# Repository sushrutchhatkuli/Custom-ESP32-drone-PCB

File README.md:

# Cheap Drone

I designed a custom drone flight controller PCB based on the ESP32-WROOM-32. The board uses USB-C charging, regulated 3.3 V power delivery, and onboard IMU sensing using the MPU-6050. The PCB is currently being fabricated, and I am actively working on automatic stabilization code for my motors.

## Overview
The goal of this project was to design a low-cost, custom flight controller PCB for a quadcopter drone while gaining hands-on experience with power management, embedded hardware design, and PCB layout. Instead of using a real controller, I wanted to use a free app that can be downloaded from the App store since ESP32 supports Wifi and Bluetooth.

The design is organized into three main parts:
- Power management
- ESP32 control and programming
- Motors and sensors

## Power Management
Power management was a major focus of this design. The board uses a battery charging circuit along with a voltage regulator to safely power all components. The incoming voltage is regulated to 3.3 V using the MIC5219-3.3YM5, which supplies power to both the ESP32 and the MPU-6050.

When the board is connected to USB-C, the voltage passes through a Schottky diode (SS34) and reaches the gate of an AO3401A P-channel MOSFET. This turns the MOSFET off and disconnects the battery (+VBatt) from the system, allowing the drone to run directly from USB power while the battery is charging.

Battery charging is handled by the TP4056, which safely manages the LiPo charging process. Two LEDs connected to the TP4056 indicate whether the battery is charging or fully charged. When the USB cable is unplugged, the MOSFET automatically turns on, reconnecting the battery so it can power the system. Decoupling capacitors are placed throughout the power rails to reduce noise and improve voltage stability.

## ESP32 Control and Programming
The +VBUS line is routed before the voltage regulator so it can supply 5 V power to the CP2102 USB-to-UART converter, which requires a higher voltage than the ESP32.

The USB data lines (D+ and D−) carry compiled code from the computer to the CP2102. The CP2102 converts this USB data into UART signals (TX and RX) that are sent to the ESP32. The RTS and DTR signals from the CP2102 pass through a 2N7002DW MOSFET, which automatically controls the EN and BOOT pins of the ESP32 during programming. This allows the ESP32 to enter firmware upload mode automatically and return to normal operation later without manual button presses.

The ESP32 acts as the main controller of the drone. It processes sensor data, controls motor outputs, and manages the overall behavior of the system. Orientation data from the MPU-6050 is used to adjust motor speeds for stabilization. I also added a UART2 (RXD2/TXD2) connector for future expansion and a four-channel SRV connector for motor control signals. Decoupling capacitors here on the 3.3 V rail help minimize noise from switching components.

## Motors and Sensors
The MPU-6050 is used as a 6-axis IMU to measure acceleration and angular velocity. It communicates with the ESP32 over I²C using the SDA and SCL lines, with pull-up resistors included to ensure reliable communication. The sensor operates at 3.3 V and is powered from the regulated supply.

The MPU-6050 does not control the motors directly. Instead, it sends motion data to the ESP32, which determines how each motor should respond to keep the drone stable. The motors are powered directly from the battery (+VBatt) because they require higher current than the logic circuitry.

Each motor is driven using an SI2302 N-channel MOSFET, allowing low-power control signals from the ESP32 to switch high-current motor loads. The MOSFET gates are driven by the ESP32, the sources are connected to ground, and the drains connect to the motors and battery supply. Since motors generate voltage spikes when switching, flyback diodes are included to protect the MOSFETs and surrounding components.

## Current Status
- Schematic and PCB design completed
- All ERC and DRC checks passed
- PCB fabrication and soldering the components in progress
- Automatic stabilization firmware under development

## Future Work
- Adding object-tracking cameras
- 3D Mapping using SLAM
- Perform flight testing and tuning
- Rev B PCB improvements based on test results

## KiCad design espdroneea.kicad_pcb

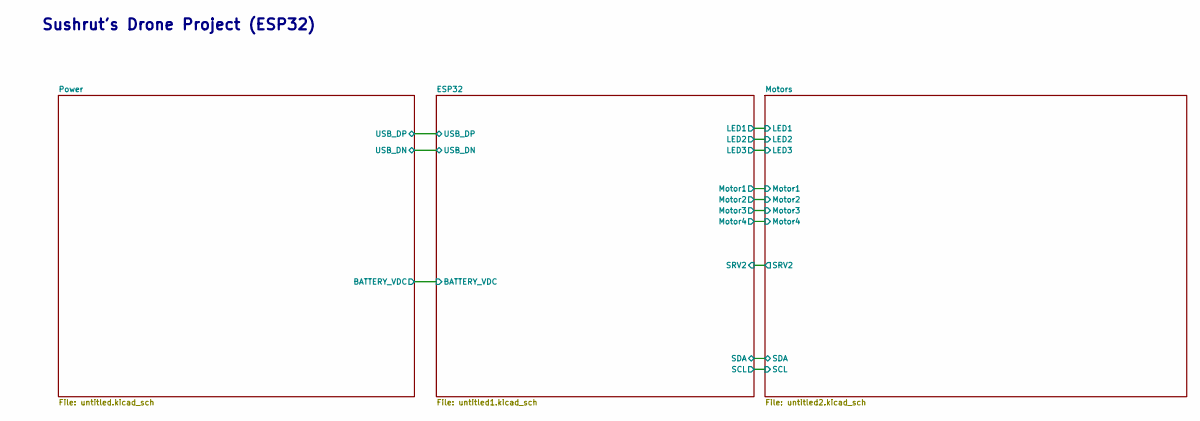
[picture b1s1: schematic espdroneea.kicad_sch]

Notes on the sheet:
Sushrut's Drone Project (ESP32)

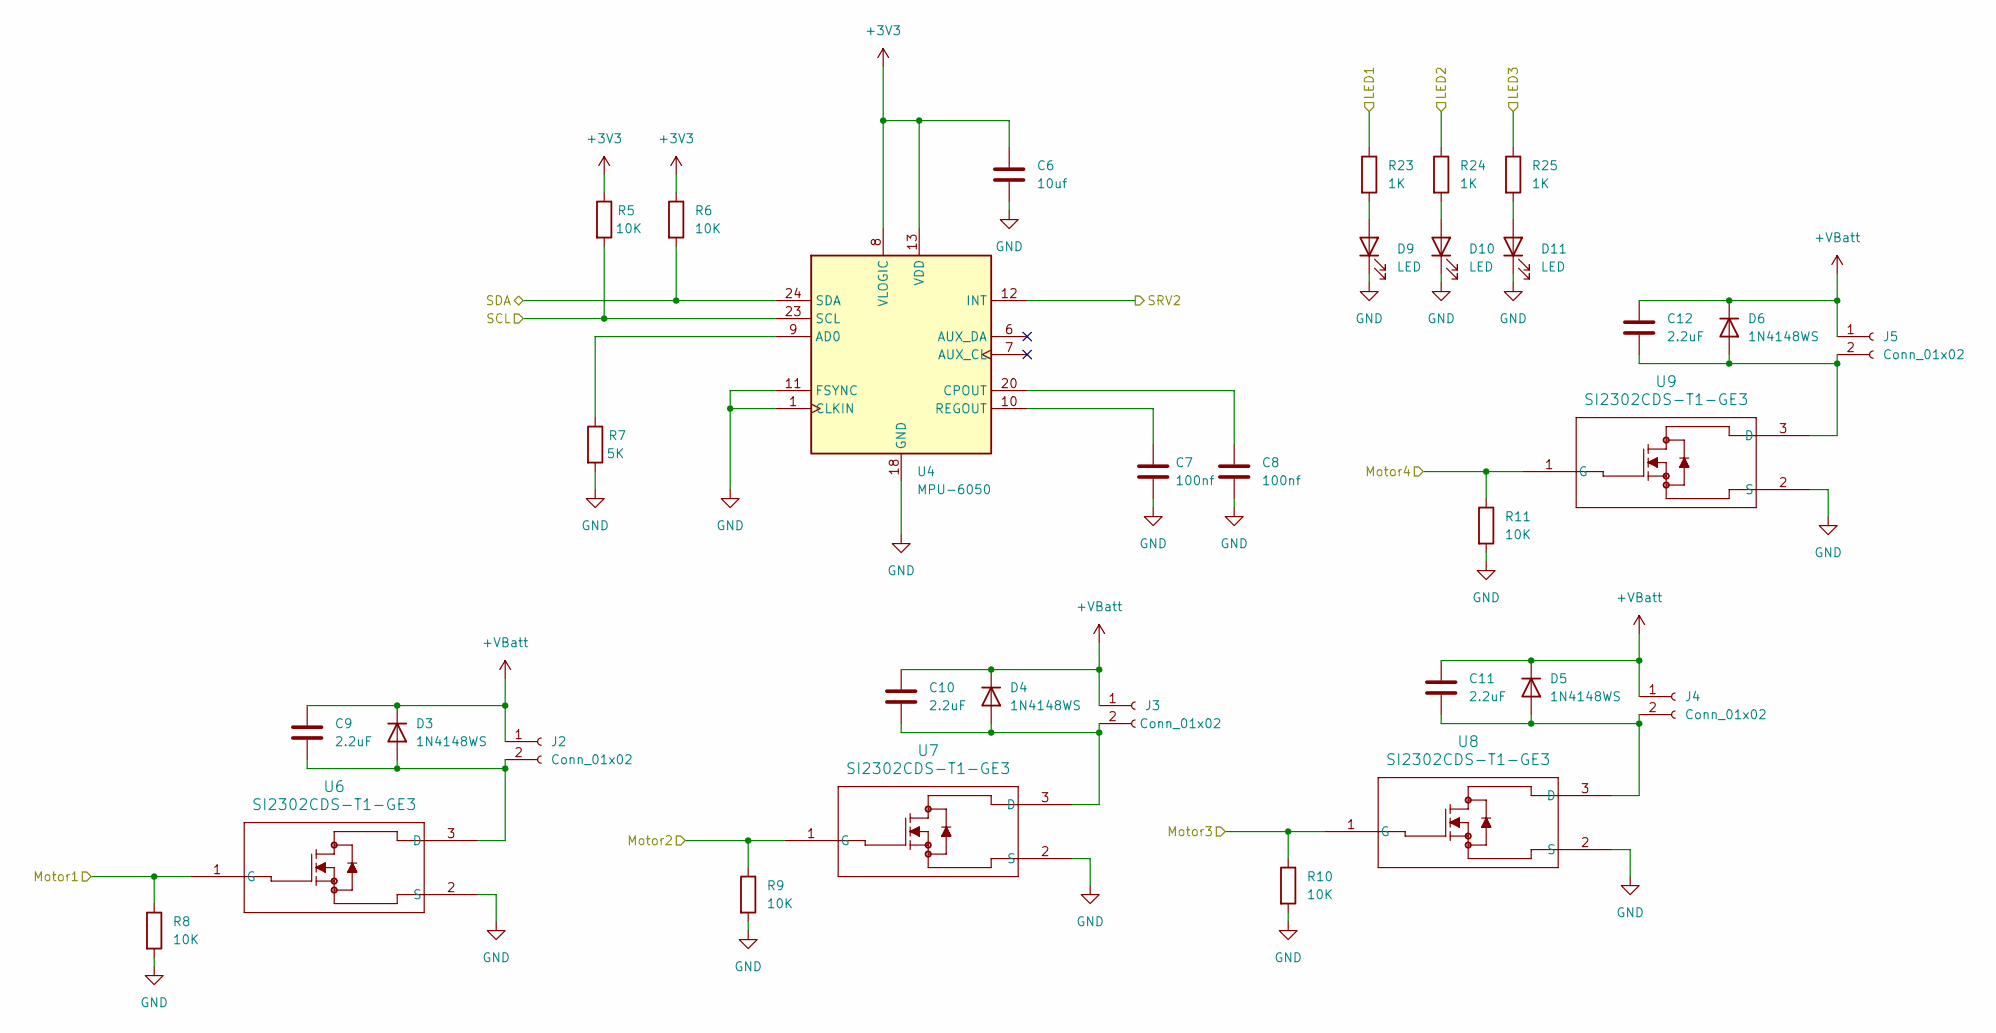
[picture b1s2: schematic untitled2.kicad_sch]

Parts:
C6: 10uf; C_0603_1608Metric
C7, C8: 100nf; C_0603_1608Metric
C9, C10, C11, C12: 2.2uF; C_0603_1608Metric
D3, D4, D5, D6: 1N4148WS; D_SOD-323
D9, D10, D11: LED; LED_0603_1608Metric
J2, J3, J4, J5: Conn_01x02; JST_GH_SM02B-GHS-TB_1x02-1MP_P1.25mm_Horizontal
R5, R6, R8, R9, R10, R11: 10K; R_0603_1608Metric
R7: 5K; R_0603_1608Metric
R23, R24, R25: 1K; R_0603_1608Metric
U4: MPU-6050; InvenSense_QFN-24_4x4mm_P0.5mm
U6, U7, U8, U9: SI2302CDS-T1-GE3; TO-236_VIS

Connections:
+3V3: C6.1, R5.1, R6.1, U4.8 (VLOGIC), U4.13 (VDD); also elsewhere on the board
+VBatt: C9.1, C10.1, C11.1, C12.1, D3.1 (K), D4.1 (K), D5.1 (K), D6.1 (K), J2.1, J3.1, J4.1, J5.1; also elsewhere on the board
/ESP32/LED1: R23.1; also elsewhere on the board
/ESP32/LED2: R24.1; also elsewhere on the board
/ESP32/LED3: R25.1; also elsewhere on the board
/ESP32/Motor1: R8.1, U6.1 (G); also elsewhere on the board
/ESP32/Motor2: R9.1, U7.1 (G); also elsewhere on the board
/ESP32/Motor3: R10.1, U8.1 (G); also elsewhere on the board
/ESP32/Motor4: R11.1, U9.1 (G); also elsewhere on the board
/ESP32/SCL: R5.2, U4.23 (SCL); also elsewhere on the board
/ESP32/SDA: R6.2, U4.24 (SDA); also elsewhere on the board
/ESP32/SRV2: U4.12 (INT); also elsewhere on the board
GND: C6.2, C7.2, C8.2, D9.1 (K), D10.1 (K), D11.1 (K), R7.2, R8.2, R9.2, R10.2, R11.2, U4.1 (CLKIN), U4.11 (FSYNC), U4.18 (GND), U6.2 (S), U7.2 (S), U8.2 (S), U9.2 (S); also elsewhere on the board
unnamed: C9.2, D3.2 (A), J2.2, U6.3 (D)
unnamed: C10.2, D4.2 (A), J3.2, U7.3 (D)
unnamed: C11.2, D5.2 (A), J4.2, U8.3 (D)
unnamed: C12.2, D6.2 (A), J5.2, U9.3 (D)
unnamed: D9.2 (A), R23.2
unnamed: D10.2 (A), R24.2
unnamed: D11.2 (A), R25.2
unnamed: R7.1, U4.9 (AD0)
unnamed: C8.1, U4.20 (CPOUT)
unnamed: C7.1, U4.10 (REGOUT)

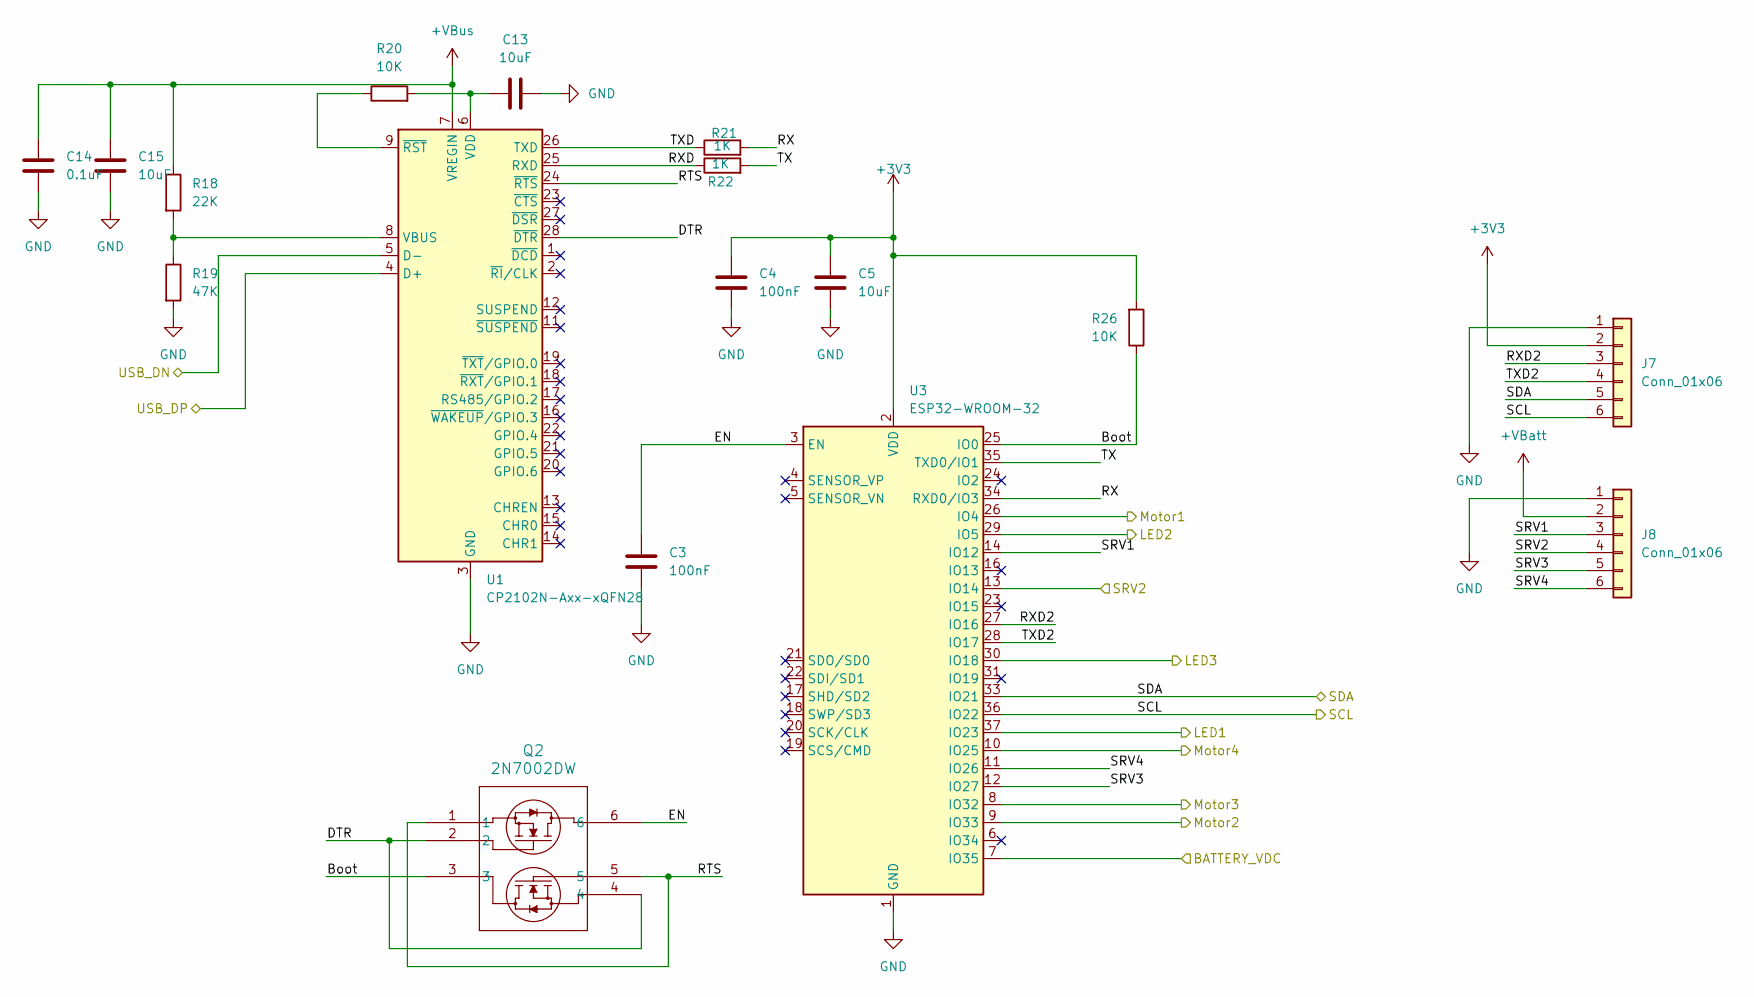
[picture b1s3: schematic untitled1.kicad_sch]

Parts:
C3, C4: 100nF; C_0603_1608Metric
C5, C13, C15: 10uF; C_0603_1608Metric
C14: 0.1uF; C_0603_1608Metric
J7, J8: Conn_01x06; PinHeader_1x06_P2.54mm_Vertical
Q2: 2N7002DW; SOT-23-6
R18: 22K; R_0603_1608Metric
R19: 47K; R_0603_1608Metric
R20, R26: 10K; R_0603_1608Metric
R21, R22: 1K; R_0603_1608Metric
U1: CP2102N-Axx-xQFN28; QFN-28-1EP_5x5mm_P0.5mm_EP3.35x3.35mm
U3: ESP32-WROOM-32

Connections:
+3V3: C4.1, C5.1, J7.2, R26.2, U3.2 (VDD); also elsewhere on the board
+VBatt: J8.2; also elsewhere on the board
+VBus: C14.1, C15.1, R18.1, U1.7 (VREGIN); also elsewhere on the board
/ESP32/BATTERY_VDC: U3.7 (IO35); also elsewhere on the board
/ESP32/Boot: Q2.3, R26.1, U3.25 (IO0)
/ESP32/DTR: Q2.2, Q2.4, U1.28 (~DTR)
/ESP32/EN: C3.1, Q2.6, U3.3 (EN)
/ESP32/LED1: U3.37 (IO23); also elsewhere on the board
/ESP32/LED2: U3.29 (IO5); also elsewhere on the board
/ESP32/LED3: U3.30 (IO18); also elsewhere on the board
/ESP32/Motor1: U3.26 (IO4); also elsewhere on the board
/ESP32/Motor2: U3.9 (IO33); also elsewhere on the board
/ESP32/Motor3: U3.8 (IO32); also elsewhere on the board
/ESP32/Motor4: U3.10 (IO25); also elsewhere on the board
/ESP32/RTS: Q2.1, Q2.5, U1.24 (~RTS)
/ESP32/RX: R21.2, U3.34 (RXD0/IO3)
/ESP32/RXD: R22.1, U1.25 (RXD)
/ESP32/RXD2: J7.3, U3.27 (IO16)
/ESP32/SCL: J7.6, U3.36 (IO22); also elsewhere on the board
/ESP32/SDA: J7.5, U3.33 (IO21); also elsewhere on the board
/ESP32/SRV1: J8.3, U3.14 (IO12)
/ESP32/SRV2: J8.4, U3.13 (IO14); also elsewhere on the board
/ESP32/SRV3: J8.5, U3.12 (IO27)
/ESP32/SRV4: J8.6, U3.11 (IO26)
/ESP32/TX: R22.2, U3.35 (TXD0/IO1)
/ESP32/TXD: R21.1, U1.26 (TXD)
/ESP32/TXD2: J7.4, U3.28 (IO17)
/ESP32/USB_DN: U1.5 (D-); also elsewhere on the board
/ESP32/USB_DP: U1.4 (D+); also elsewhere on the board
GND: C3.2, C4.2, C5.2, C13.2, C14.2, C15.2, J7.1, J8.1, R19.2, U1.3 (GND), U1.29 (GND), U3.1 (GND), U3.15 (GND), U3.38 (GND), U3.39 (GND); also elsewhere on the board
unnamed: R18.2, R19.1, U1.8 (VBUS)
unnamed: C13.1, R20.2, U1.6 (VDD)
unnamed: R20.1, U1.9 (~RST)

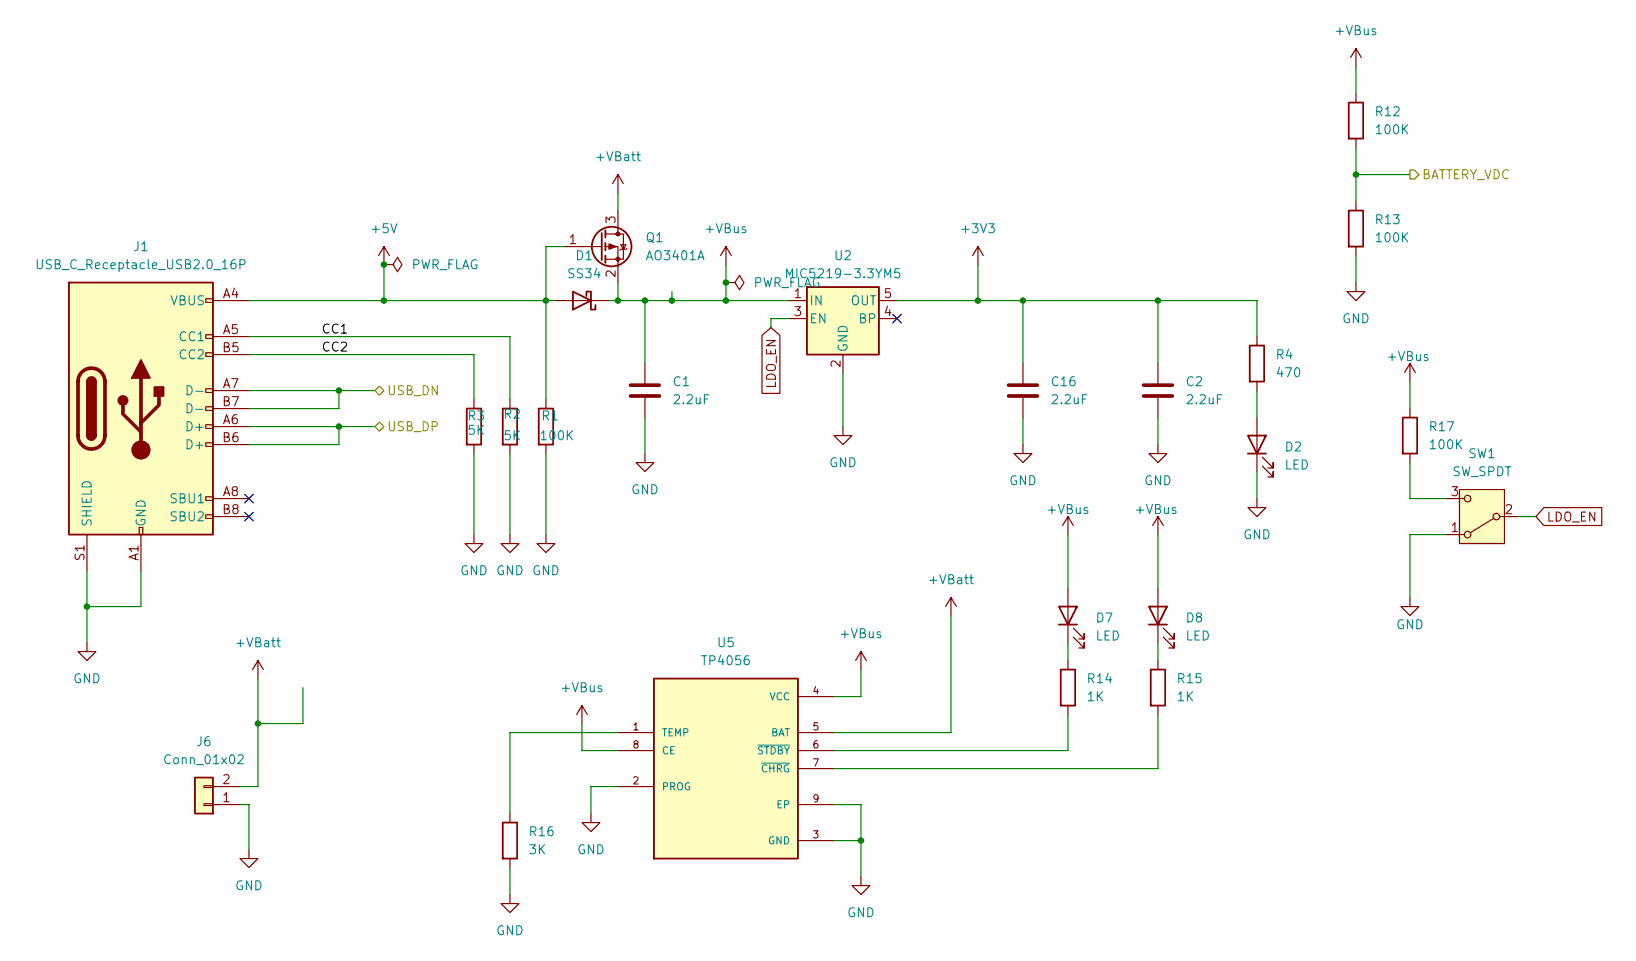
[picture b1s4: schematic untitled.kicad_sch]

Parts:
C1, C2, C16: 2.2uF; C_0603_1608Metric
D1: SS34; D_SMA
D2, D7, D8: LED; LED_0603_1608Metric
J1: USB_C_Receptacle_USB2.0_16P; USB_C_Receptacle_HRO_TYPE-C-31-M-12
J6: Conn_01x02; JST_GH_SM02B-GHS-TB_1x02-1MP_P1.25mm_Horizontal
Q1: AO3401A; SOT-23
R1, R12, R13, R17: 100K; R_0603_1608Metric
R2, R3: 5K; R_0603_1608Metric
R4: 470; R_0603_1608Metric
R14, R15: 1K; R_0603_1608Metric
R16: 3K; R_0603_1608Metric
SW1: SW_SPDT; SW_SPDT_PCM12
U2: MIC5219-3.3YM5; SOT-23-5
U5: TP4056; SOP127P600X175-9N

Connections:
+3V3: C2.1, C16.1, R4.1, U2.5 (OUT); also elsewhere on the board
+5V: D1.2 (A), J1.A4 (VBUS), J1.A9 (VBUS), J1.B4 (VBUS), J1.B9 (VBUS), Q1.1 (G), R1.1
+VBatt: J6.2, Q1.3 (D), U5.5 (BAT); also elsewhere on the board
+VBus: C1.1, D1.1 (K), D7.2 (A), D8.2 (A), Q1.2 (S), R12.1, R17.1, U2.1 (IN), U5.4 (VCC), U5.8 (CE); also elsewhere on the board
/ESP32/BATTERY_VDC: R12.2, R13.1; also elsewhere on the board
/ESP32/USB_DN: J1.A7 (D-), J1.B7 (D-); also elsewhere on the board
/ESP32/USB_DP: J1.A6 (D+), J1.B6 (D+); also elsewhere on the board
/Power/CC1: J1.A5 (CC1), R2.1
/Power/CC2: J1.B5 (CC2), R3.1
GND: C1.2, C2.2, C16.2, D2.1 (K), J1.A1 (GND), J1.A12 (GND), J1.B1 (GND), J1.B12 (GND), J1.S1 (SHIELD), J6.1, R1.2, R2.2, R3.2, R13.2, R16.2, SW1.1 (A), U2.2 (GND), U5.2 (PROG), U5.3 (GND), U5.9 (EP); also elsewhere on the board
LDO_EN: SW1.2 (B), U2.3 (EN)
unnamed: D2.2 (A), R4.2
unnamed: D7.1 (K), R14.1
unnamed: D8.1 (K), R15.1
unnamed: R17.2, SW1.3 (C)
unnamed: R16.1, U5.1 (TEMP)
unnamed: R15.2, U5.7 (~CHRG)
unnamed: R14.2, U5.6 (~STDBY)

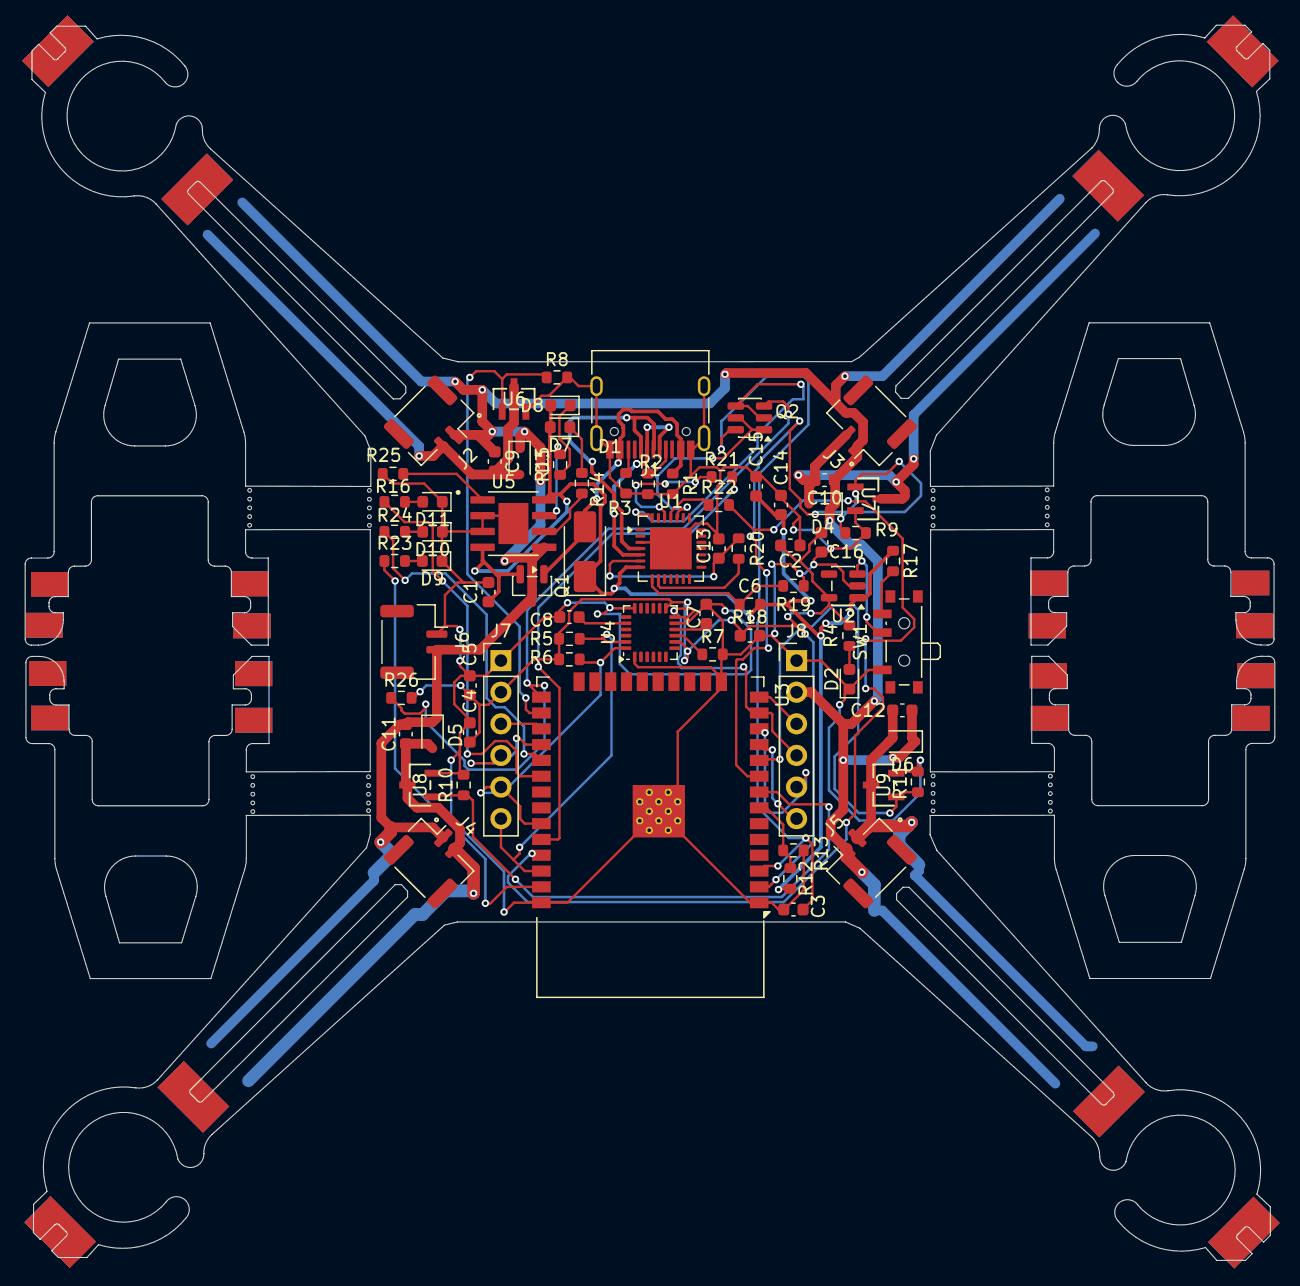
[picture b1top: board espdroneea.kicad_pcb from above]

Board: 2 copper layers, 100.4 x 99.2 mm, 73 parts (0 on the bottom side), 54 nets.

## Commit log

2026-01-14 Organizing with folders
2026-01-14 Create pcb
2026-01-14 Create Production
2026-01-14 Create idk
2026-01-14 Create i
2026-01-14 Fabrication
2026-01-14 schematics
2026-01-14 3D View
2026-01-14 README.md
2026-01-14 footprints
2026-01-14 Create footprints
2026-01-14 symbols
2026-01-15 Create backupDrone
2026-01-15 Create A
2026-01-17 Add files via upload
    Bill of Materials (BOM)
